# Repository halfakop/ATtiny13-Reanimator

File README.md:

# Печатная плата реаниматора для ATtiny13

Плата разработана с помощью Eagle 6.6.

Для восстановления работоспособности заблокированной ATtiny13, её
следует вставить в колодку или прижать к контактам на плате (для SMD),
затем подать питание (12В) на плату. Восстановление микроконтроллёра
происходит при подаче питания и при нажатии кнопки Reanimate.

Устройство собрано по мотивам сайта [РадиоДЕД](http://radioded.ru/skhema-na-mikrokontrollere/reanimator-mikrokontrollerov-avr-attiny13).

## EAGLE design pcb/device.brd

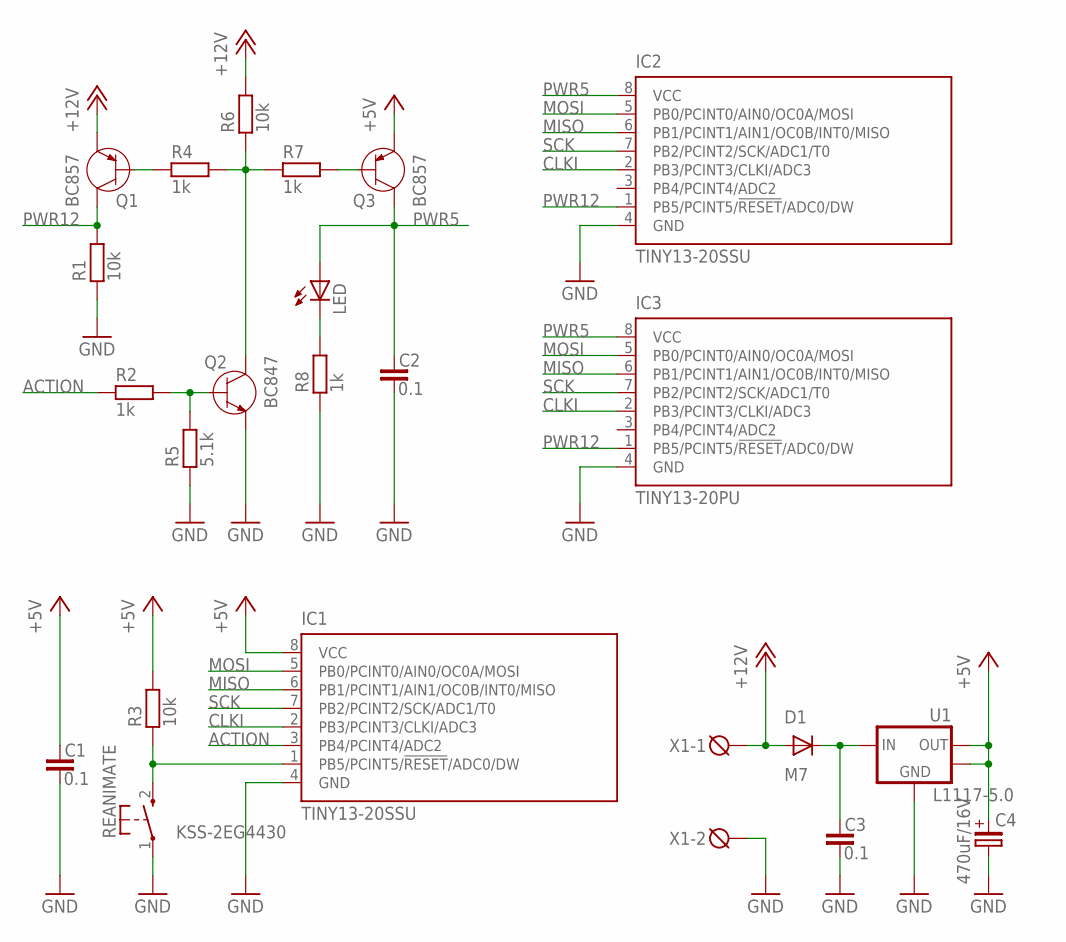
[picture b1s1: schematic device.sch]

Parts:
C1, C2, C3: 0.1; C0805
C4: 470uF/16V; C175TMP-0810
D1: M7; DO214AC
IC1, IC2: TINY13-20SSU; 8S1
IC3: TINY13-20PU; DIL08
LED: LEDCHIPLED_0805; CHIPLED_0805
Q1, Q3: BC857; SOT23
Q2: BC847; SOT23
R1, R3, R6: 10k; R0805
R2, R4, R7, R8: 1k; R0805
R5: 5.1k; R0805
REANIMATE: KSS-2EG4430
U1: L1117-5.0; SOT223
X1: DG3XX-02-5.0; DG306-5.0-02P

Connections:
+5V: C1.1, C4.+, IC1.8 (VCC), Q3.2 (E), R3.2, U1.2 (OUT), U1.4 (MASS)
+12V: D1.A, Q1.2 (E), R6.2, X1.1
ACTION: IC1.3 (PB4/PCINT4/ADC2), R2.1
CLKI: IC1.2 (PB3/PCINT3/CLKI/ADC3), IC2.2 (PB3/PCINT3/CLKI/ADC3), IC3.2 (PB3/PCINT3/CLKI/ADC3)
GND: C1.2, C2.2, C3.2, C4.-, IC1.4 (GND), IC2.4 (GND), IC3.4 (GND), Q2.2 (E), R1.1, R5.1, R8.1, REANIMATE.1, U1.1 (GND), X1.2
MISO: IC1.6 (PB1/PCINT1/AIN1/OC0B/INT0/MISO), IC2.6 (PB1/PCINT1/AIN1/OC0B/INT0/MISO), IC3.6 (PB1/PCINT1/AIN1/OC0B/INT0/MISO)
MOSI: IC1.5 (PB0/PCINT0/AIN0/OC0A/MOSI), IC2.5 (PB0/PCINT0/AIN0/OC0A/MOSI), IC3.5 (PB0/PCINT0/AIN0/OC0A/MOSI)
unnamed: IC1.1 (PB5/PCINT5/!RESET!/ADC0/DW), R3.1, REANIMATE.2 (S)
unnamed: C3.1, D1.C, U1.3 (IN)
unnamed: Q2.1 (B), R2.2, R5.2
unnamed: Q1.1 (B), R4.1
unnamed: Q3.1 (B), R7.2
unnamed: LED.C, R8.2
unnamed: Q2.3 (C), R4.2, R6.1, R7.1
PWR5: C2.1, IC2.8 (VCC), IC3.8 (VCC), LED.A, Q3.3 (C)
PWR12: IC2.1 (PB5/PCINT5/!RESET!/ADC0/DW), IC3.1 (PB5/PCINT5/!RESET!/ADC0/DW), Q1.3 (C), R1.2
SCK: IC1.7 (PB2/PCINT2/SCK/ADC1/T0), IC2.7 (PB2/PCINT2/SCK/ADC1/T0), IC3.7 (PB2/PCINT2/SCK/ADC1/T0)

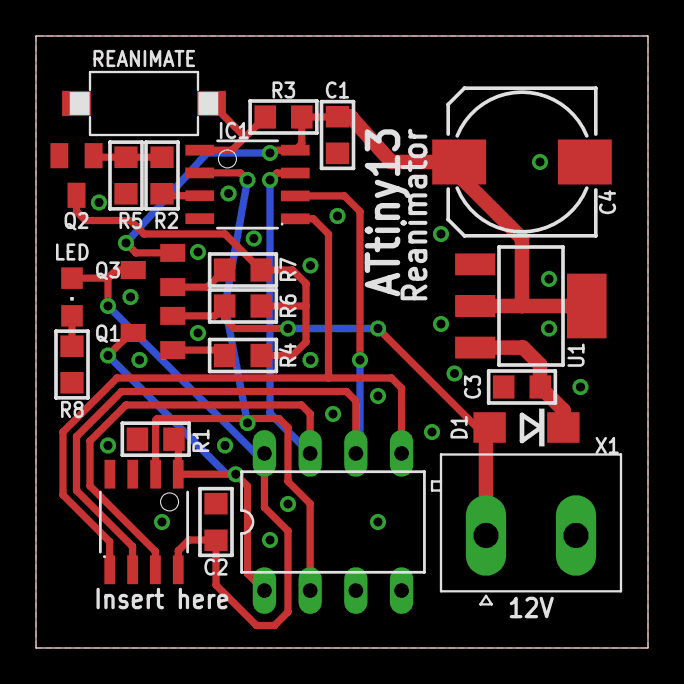
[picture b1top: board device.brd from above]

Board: 2 copper layers, 34.0 x 34.0 mm, 23 parts (0 on the bottom side), 17 nets.

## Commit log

2014-11-29 Project description.
2014-11-29 Schematic and Board.
2014-11-29 Gerber files and visualisation.
2014-11-29 Firmware.
2014-11-29 Simple wrapper.
